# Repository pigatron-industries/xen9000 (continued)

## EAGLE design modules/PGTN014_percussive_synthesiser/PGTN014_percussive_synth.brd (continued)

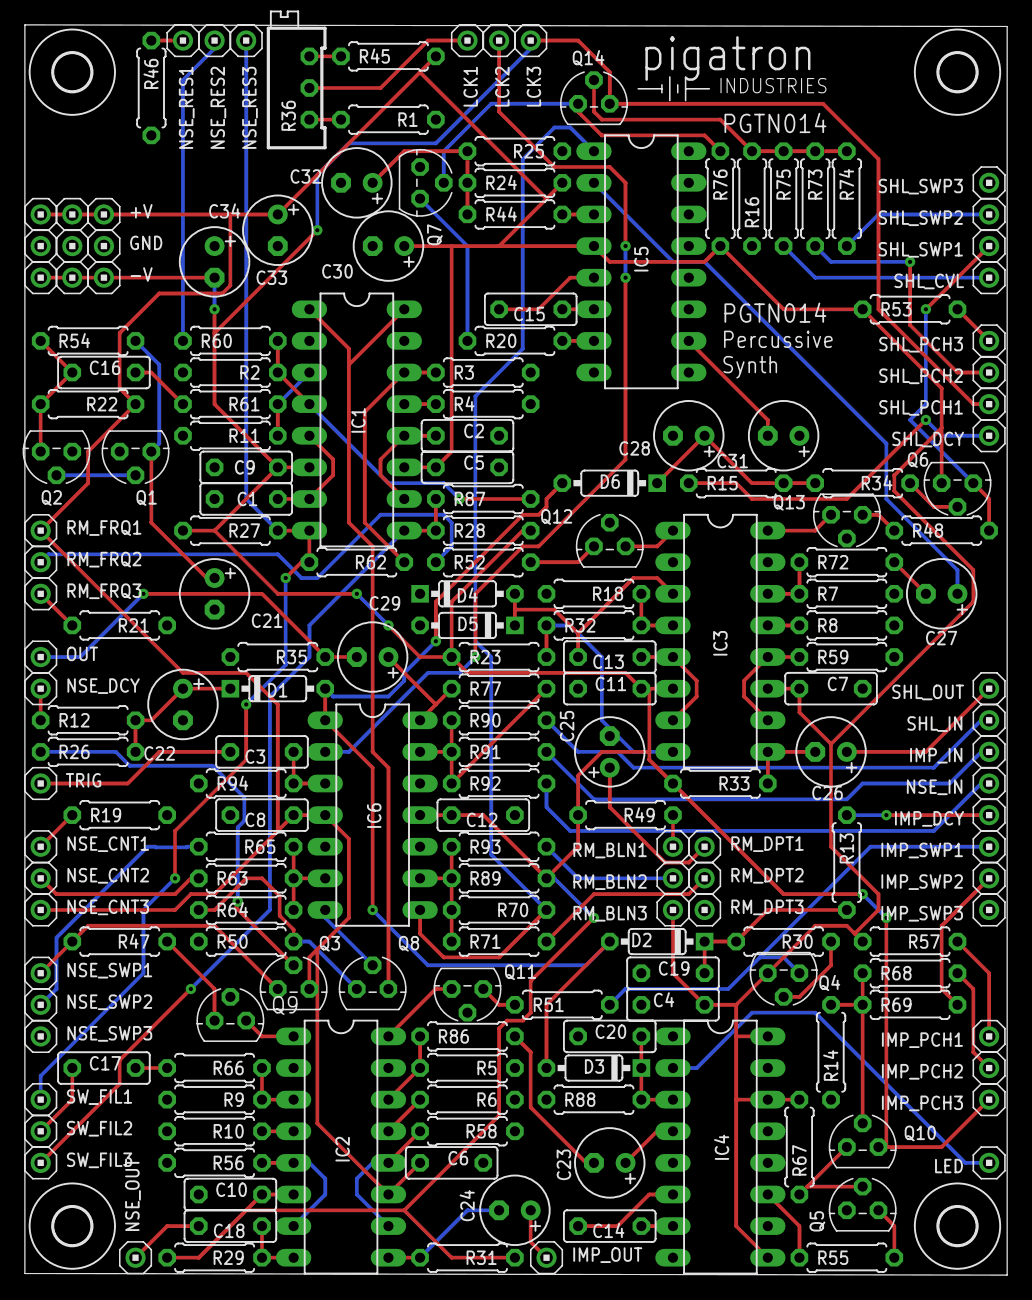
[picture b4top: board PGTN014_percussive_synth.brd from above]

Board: 2 copper layers, 78.9 x 100.4 mm, 201 parts (0 on the bottom side), 114 nets.

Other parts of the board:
U$1, U$2, U$3, U$4: STANDOFF/3.0
U$5: PIGATRON-LOGO

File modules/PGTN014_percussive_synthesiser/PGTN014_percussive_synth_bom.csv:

"Qty";"Value";"Device";"Package";"Parts";"Description";"SPICEPREFIX";
"1";"";"TRIMMER64X";"TRIMMER/64B";"R36";"Trimm resistor";"";
"1";"100R";"RESISTORRESISTOR/UPRIGHT/7.5";"RESISTOR/7.5";"R1";"RESISTOR, European symbol";"";
"18";"100k";"RESISTORRESISTOR/UPRIGHT/7.5";"RESISTOR/7.5";"R60, R61, R62, R63, R64, R65, R66, R67, R68, R69, R70, R71, R72, R73, R74, R75, R76, R77";"RESISTOR, European symbol";"";
"5";"100nF";"CAPACITORCERAMICDISC/5";"CERAMICDISC/5";"C16, C17, C18, C19, C20";"CAPACITOR, European symbol";"";
"10";"10k";"RESISTORRESISTOR/UPRIGHT/7.5";"RESISTOR/7.5";"R16, R26, R27, R28, R29, R30, R31, R32, R33, R34";"RESISTOR, European symbol";"";
"10";"10nF";"CAPACITORCERAMICDISC/5";"CERAMICDISC/5";"C4, C5, C6, C7, C8, C9, C10, C11, C12, C13";"CAPACITOR, European symbol";"";
"4";"10uF";"CAPACITOR/POLARIZEDE2.5-6";"E2,5-6";"C31, C32, C33, C34";"POLARIZED CAPACITOR, European symbol";"C";
"1";"12k";"RESISTORRESISTOR/UPRIGHT/7.5";"RESISTOR/7.5";"R44";"RESISTOR, European symbol";"";
"1";"180k";"RESISTORRESISTOR/UPRIGHT/7.5";"RESISTOR/7.5";"R86";"RESISTOR, European symbol";"";
"1";"1M";"RESISTORRESISTOR/UPRIGHT/7.5";"RESISTOR/7.5";"R94";"RESISTOR, European symbol";"";
"6";"1N4148";"1N4148DO35-7";"DO35-7";"D1, D2, D3, D4, D5, D6";"DIODE";"";
"4";"1k";"RESISTORRESISTOR/UPRIGHT/7.5";"RESISTOR/7.5";"R12, R13, R14, R15";"RESISTOR, European symbol";"";
"1";"1nF";"CAPACITORCERAMICDISC/5";"CERAMICDISC/5";"C3";"CAPACITOR, European symbol";"";
"2";"2.2k";"RESISTORRESISTOR/UPRIGHT/7.5";"RESISTOR/7.5";"R19, R20";"RESISTOR, European symbol";"";
"9";"2.2uF";"CAPACITOR/POLARIZEDE2.5-6";"E2,5-6";"C21, C22, C23, C24, C25, C26, C27, C28, C29";"POLARIZED CAPACITOR, European symbol";"C";
"6";"200k";"RESISTORRESISTOR/UPRIGHT/7.5";"RESISTOR/7.5";"R87, R88, R89, R90, R91, R92";"RESISTOR, European symbol";"";
"5";"20k";"RESISTORRESISTOR/UPRIGHT/7.5";"RESISTOR/7.5";"R35, R45, R46, R47, R48";"RESISTOR, European symbol";"";
"5";"220R";"RESISTORRESISTOR/UPRIGHT/7.5";"RESISTOR/7.5";"R2, R3, R4, R5, R6";"RESISTOR, European symbol";"";
"1";"22k";"RESISTORRESISTOR/UPRIGHT/7.5";"RESISTOR/7.5";"R49";"RESISTOR, European symbol";"";
"2";"22nF";"CAPACITORCERAMICDISC/5";"CERAMICDISC/5";"C14, C15";"CAPACITOR, European symbol";"";
"4";"27k";"RESISTORRESISTOR/UPRIGHT/7.5";"RESISTOR/7.5";"R50, R51, R52, R53";"RESISTOR, European symbol";"";
"8";"2N3904";"2N3904";"TO92";"Q1, Q2, Q3, Q4, Q5, Q6, Q7, Q9";"NPN Transistor";"";
"6";"2N3906";"2N3906";"TO92";"Q8, Q10, Q11, Q12, Q13, Q14";"PNP Transistor";"";
"1";"2k";"RESISTORRESISTOR/UPRIGHT/7.5";"RESISTOR/7.5";"R18";"RESISTOR, European symbol";"";
"1";"3.9k";"RESISTORRESISTOR/UPRIGHT/7.5";"RESISTOR/7.5";"R21";"RESISTOR, European symbol";"";
"1";"330k";"RESISTORRESISTOR/UPRIGHT/7.5";"RESISTOR/7.5";"R93";"RESISTOR, European symbol";"";
"2";"390R";"RESISTORRESISTOR/UPRIGHT/7.5";"RESISTOR/7.5";"R7, R8";"RESISTOR, European symbol";"";
"1";"4.7k";"RESISTORRESISTOR/UPRIGHT/7.5";"RESISTOR/7.5";"R22";"RESISTOR, European symbol";"";
"1";"4.7uF";"CAPACITOR/POLARIZEDE2.5-6";"E2,5-6";"C30";"POLARIZED CAPACITOR, European symbol";"C";
"1";"4046N";"4046N";"DIL16";"IC4";"Micropower PLL";"";
"2";"47k";"RESISTORRESISTOR/UPRIGHT/7.5";"RESISTOR/7.5";"R54, R55";"RESISTOR, European symbol";"";
"3";"5.1k";"RESISTORRESISTOR/UPRIGHT/7.5";"RESISTOR/7.5";"R23, R24, R25";"RESISTOR, European symbol";"";
"2";"560R";"RESISTORRESISTOR/UPRIGHT/7.5";"RESISTOR/7.5";"R9, R10";"RESISTOR, European symbol";"";
"4";"56k";"RESISTORRESISTOR/UPRIGHT/7.5";"RESISTOR/7.5";"R56, R57, R58, R59";"RESISTOR, European symbol";"";
"1";"820R";"RESISTORRESISTOR/UPRIGHT/7.5";"RESISTOR/7.5";"R11";"RESISTOR, European symbol";"";
"2";"820pF";"CAPACITORCERAMICDISC/5";"CERAMICDISC/5";"C1, C2";"CAPACITOR, European symbol";"";
"58";"HEADER/MALE/01";"HEADER/MALE/01";"HEADER/MALE/01";"+V, +V2, +V3, -V, -V2, -V3, GND, GND2, GND3, IMP_DCY, IMP_IN, IMP_OUT, IMP_PCH1, IMP_PCH2, IMP_PCH3, IMP_SWP1, IMP_SWP2, IMP_SWP3, LCK1, LCK2, LCK3, LED, NSE_CNT1, NSE_CNT2, NSE_CNT3, NSE_DCY, NSE_IN, NSE_OUT, NSE_RES1, NSE_RES2, NSE_RES3, NSE_SWP1, NSE_SWP2, NSE_SWP3, OUT, RM_BLN1, RM_BLN2, RM_BLN3, RM_DPT1, RM_DPT2, RM_DPT3, RM_FRQ1, RM_FRQ2, RM_FRQ3, SHL_CVL, SHL_DCY, SHL_IN, SHL_OUT, SHL_PCH1, SHL_PCH2, SHL_PCH3, SHL_SWP1, SHL_SWP2, SHL_SWP3, SW_FIL1, SW_FIL2, SW_FIL3, TRIG";"";"X";
"3";"LM13700N";"LM13700N";"DIL16";"IC1, IC2, IC3";"Dual OTA with buffers";"";
"1";"TL074P";"TL074P";"DIL14";"IC6";"OP AMP";"";
"1";"XR-2206";"DIL16";"DIL16";"IC5";"Dual In Line / Socket";"";

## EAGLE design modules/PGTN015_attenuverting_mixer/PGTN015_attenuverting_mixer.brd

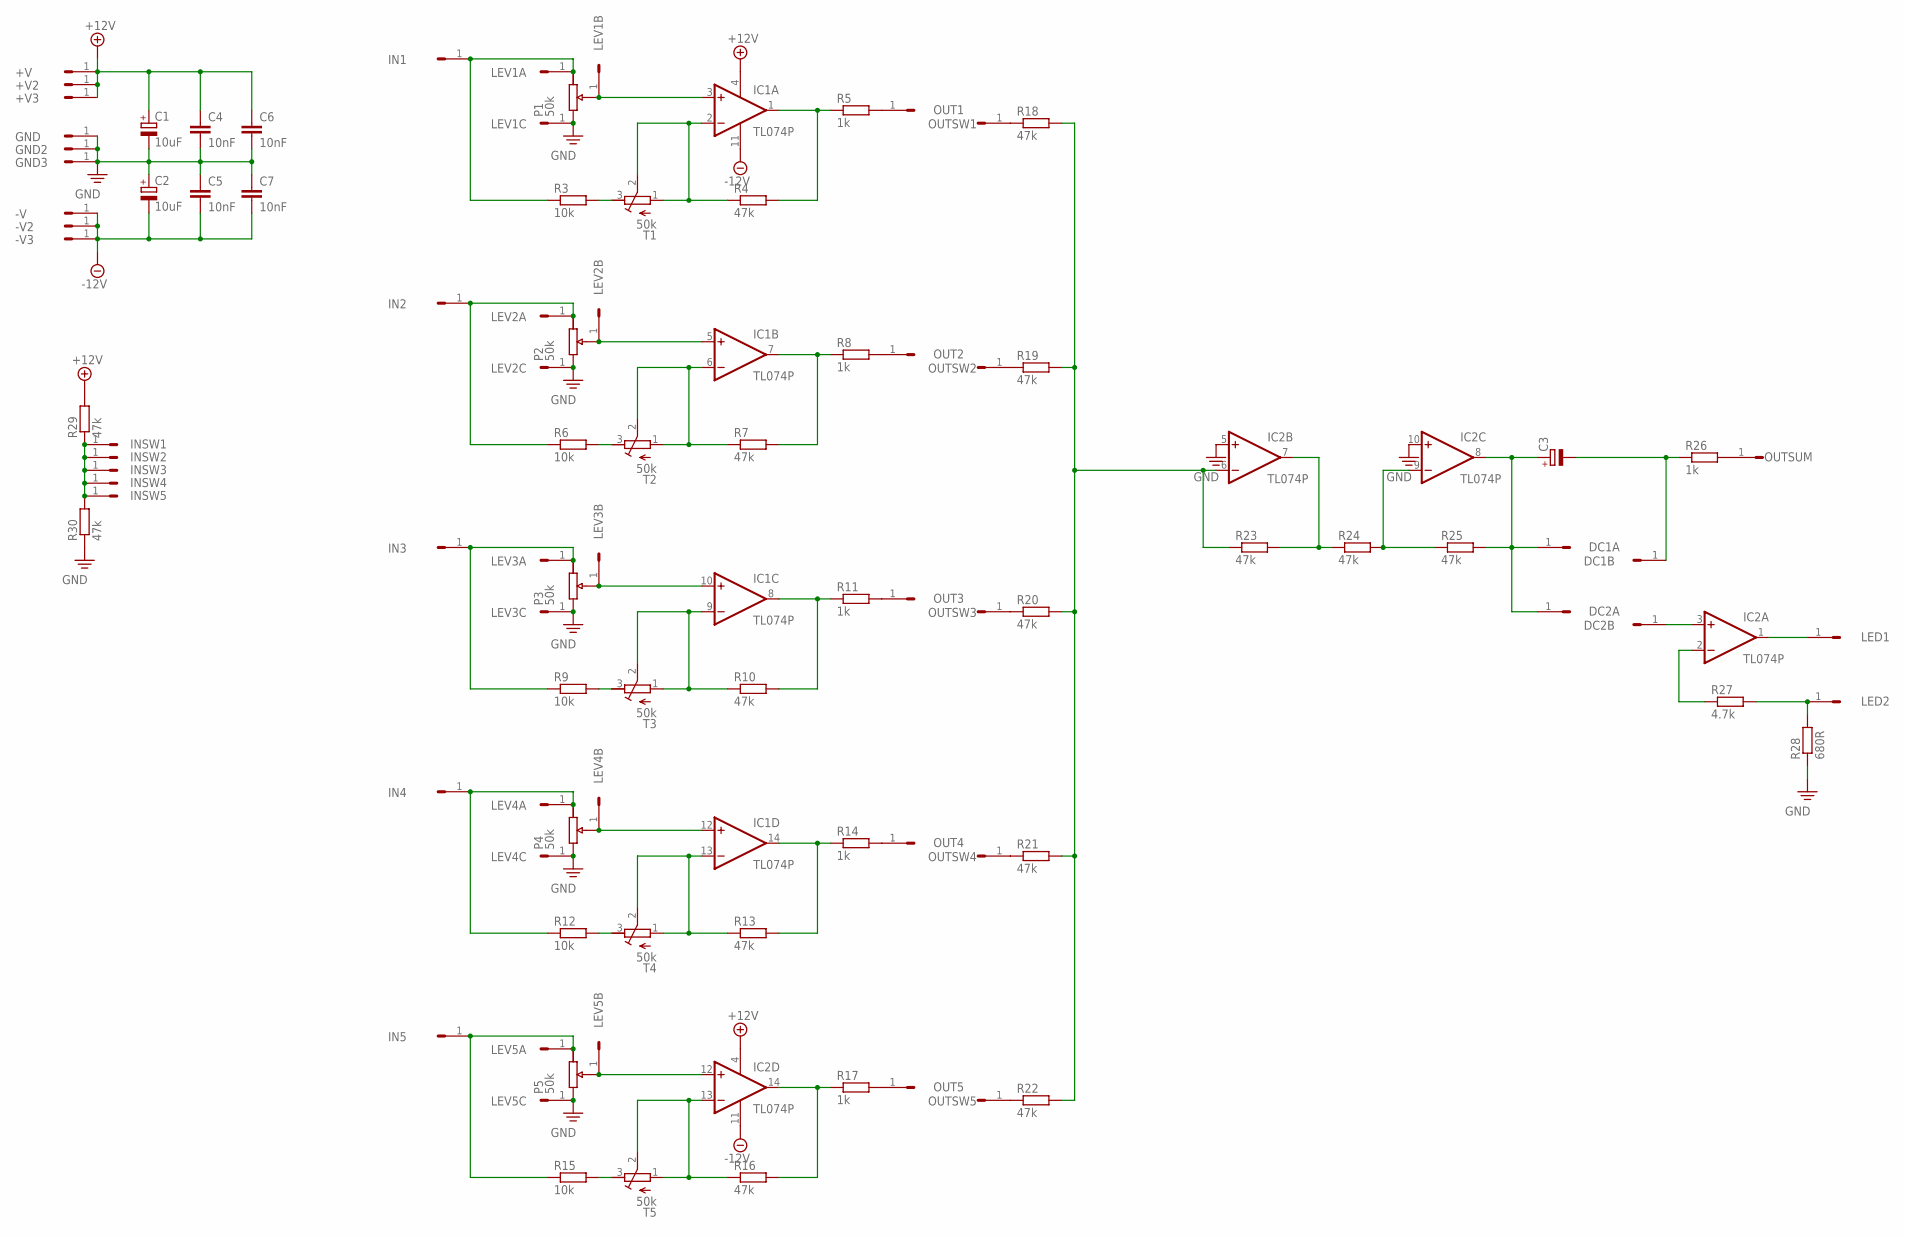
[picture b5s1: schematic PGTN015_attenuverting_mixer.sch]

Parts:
+V, +V2, +V3: HEADER/MALE/01
-V, -V2, -V3: HEADER/MALE/01
C1, C2: 10uF; E2,5-6
C3: CAPACITOR/POLARIZEDE2.5-6; E2,5-6
C4, C5, C6, C7: 10nF; CERAMICDISC/5
DC1A, DC1B, DC2A, DC2B: HEADER/MALE/01
GND, GND2, GND3: HEADER/MALE/01
IC1, IC2: TL074P; DIL14
IN1, IN2, IN3, IN4, IN5: HEADER/MALE/01
INSW1, INSW2, INSW3, INSW4, INSW5: HEADER/MALE/01
LED1, LED2: HEADER/MALE/01
LEV1A, LEV1B, LEV1C, LEV2A, LEV2B, LEV2C, LEV3A, LEV3B, LEV3C, LEV4A, LEV4B, LEV4C, LEV5A, LEV5B, LEV5C: HEADER/MALE/01
OUT1, OUT2, OUT3, OUT4, OUT5: HEADER/MALE/01
OUTSUM: HEADER/MALE/01
OUTSW1, OUTSW2, OUTSW3, OUTSW4, OUTSW5: HEADER/MALE/01
R3, R6, R9, R12, R15: 10k; RESISTOR/7.5
R4, R7, R10, R13, R16, R18, R19, R20, R21, R22, R23, R24, R25, R29, R30: 47k; RESISTOR/7.5
R5, R8, R11, R14, R17, R26: 1k; RESISTOR/7.5
R27: 4.7k; RESISTOR/7.5
R28: 680R; RESISTOR/7.5
T1, T2, T3, T4, T5: 50k; TRIMMER/64B

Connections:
+12V: +V.1, +V2.1, +V3.1, C1.+, C4.1, C6.1, IC1.4 (V+), IC2.4 (V+), R29.2
-12V: -V.1, -V2.1, -V3.1, C2.-, C5.2, C7.2, IC1.11 (V-), IC2.11 (V-)
GND: C1.-, C2.+, C4.2, C5.1, C6.2, C7.1, GND.1, GND2.1, GND3.1, IC2.5 (+IN), IC2.10 (+IN), LEV1C.1, LEV2C.1, LEV3C.1, LEV4C.1, LEV5C.1, R28.1, R30.1
unnamed: IC1.2 (-IN), R4.1, T1.1 (E), T1.2 (S)
unnamed: IC1.3 (+IN), LEV1B.1
unnamed: R3.2, T1.3 (A)
unnamed: IC1.1 (OUT), R4.2, R5.1
unnamed: IN1.1, LEV1A.1, R3.1
unnamed: OUT1.1, R5.2
unnamed: IC1.6 (-IN), R7.1, T2.1 (E), T2.2 (S)
unnamed: R6.2, T2.3 (A)
unnamed: IC1.7 (OUT), R7.2, R8.1
unnamed: IC1.5 (+IN), LEV2B.1
unnamed: IN2.1, LEV2A.1, R6.1
unnamed: OUT2.1, R8.2
unnamed: IC1.9 (-IN), R10.1, T3.1 (E), T3.2 (S)
unnamed: R9.2, T3.3 (A)
unnamed: IC1.8 (OUT), R10.2, R11.1
unnamed: IC1.10 (+IN), LEV3B.1
unnamed: IN3.1, LEV3A.1, R9.1
unnamed: OUT3.1, R11.2
unnamed: IC1.13 (-IN), R13.1, T4.1 (E), T4.2 (S)
unnamed: R12.2, T4.3 (A)
unnamed: IC1.14 (OUT), R13.2, R14.1
unnamed: IC1.12 (+IN), LEV4B.1
unnamed: IN4.1, LEV4A.1, R12.1
unnamed: OUT4.1, R14.2
unnamed: IC2.13 (-IN), R16.1, T5.1 (E), T5.2 (S)
unnamed: R15.2, T5.3 (A)
unnamed: IC2.14 (OUT), R16.2, R17.1
unnamed: IC2.12 (+IN), LEV5B.1
unnamed: IN5.1, LEV5A.1, R15.1
unnamed: OUT5.1, R17.2
unnamed: OUTSW1.1, R18.1
unnamed: OUTSW2.1, R19.1
unnamed: OUTSW3.1, R20.1
unnamed: OUTSW4.1, R21.1
unnamed: OUTSW5.1, R22.1
unnamed: C3.-, DC1B.1, R26.1
unnamed: IC2.7 (OUT), R23.2, R24.1
unnamed: IC2.6 (-IN), R18.2, R19.2, R20.2, R21.2, R22.2, R23.1
unnamed: IC2.9 (-IN), R24.2, R25.1
unnamed: C3.+, DC1A.1, DC2A.1, IC2.8 (OUT), R25.2
unnamed: OUTSUM.1, R26.2
unnamed: DC2B.1, IC2.3 (+IN)
unnamed: IC2.2 (-IN), R27.1
unnamed: LED2.1, R27.2, R28.2
unnamed: IC2.1 (OUT), LED1.1
unnamed: INSW1.1, INSW2.1, INSW3.1, INSW4.1, INSW5.1, R29.1, R30.2

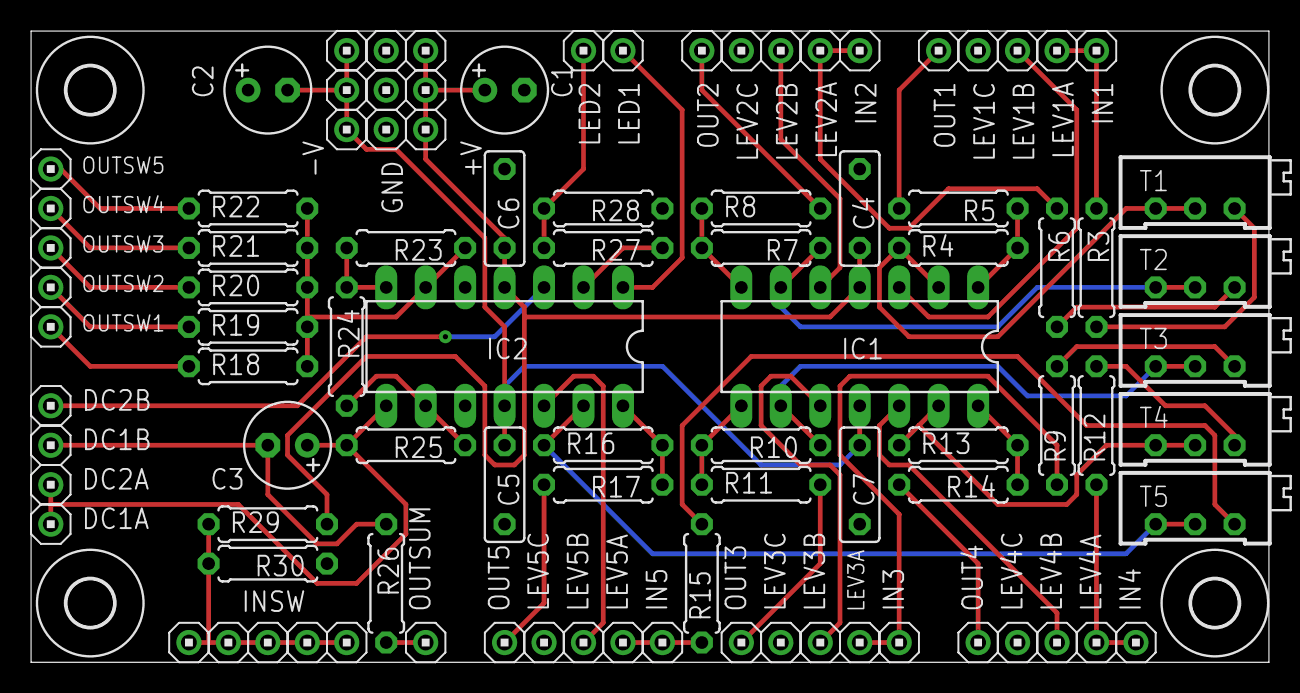
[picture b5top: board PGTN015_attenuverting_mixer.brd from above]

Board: 2 copper layers, 79.7 x 40.6 mm, 98 parts (1 on the bottom side), 49 nets.

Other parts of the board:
U$1, U$2, U$3, U$4: STANDOFF/3.0
U$5: PIGATRON-LOGO

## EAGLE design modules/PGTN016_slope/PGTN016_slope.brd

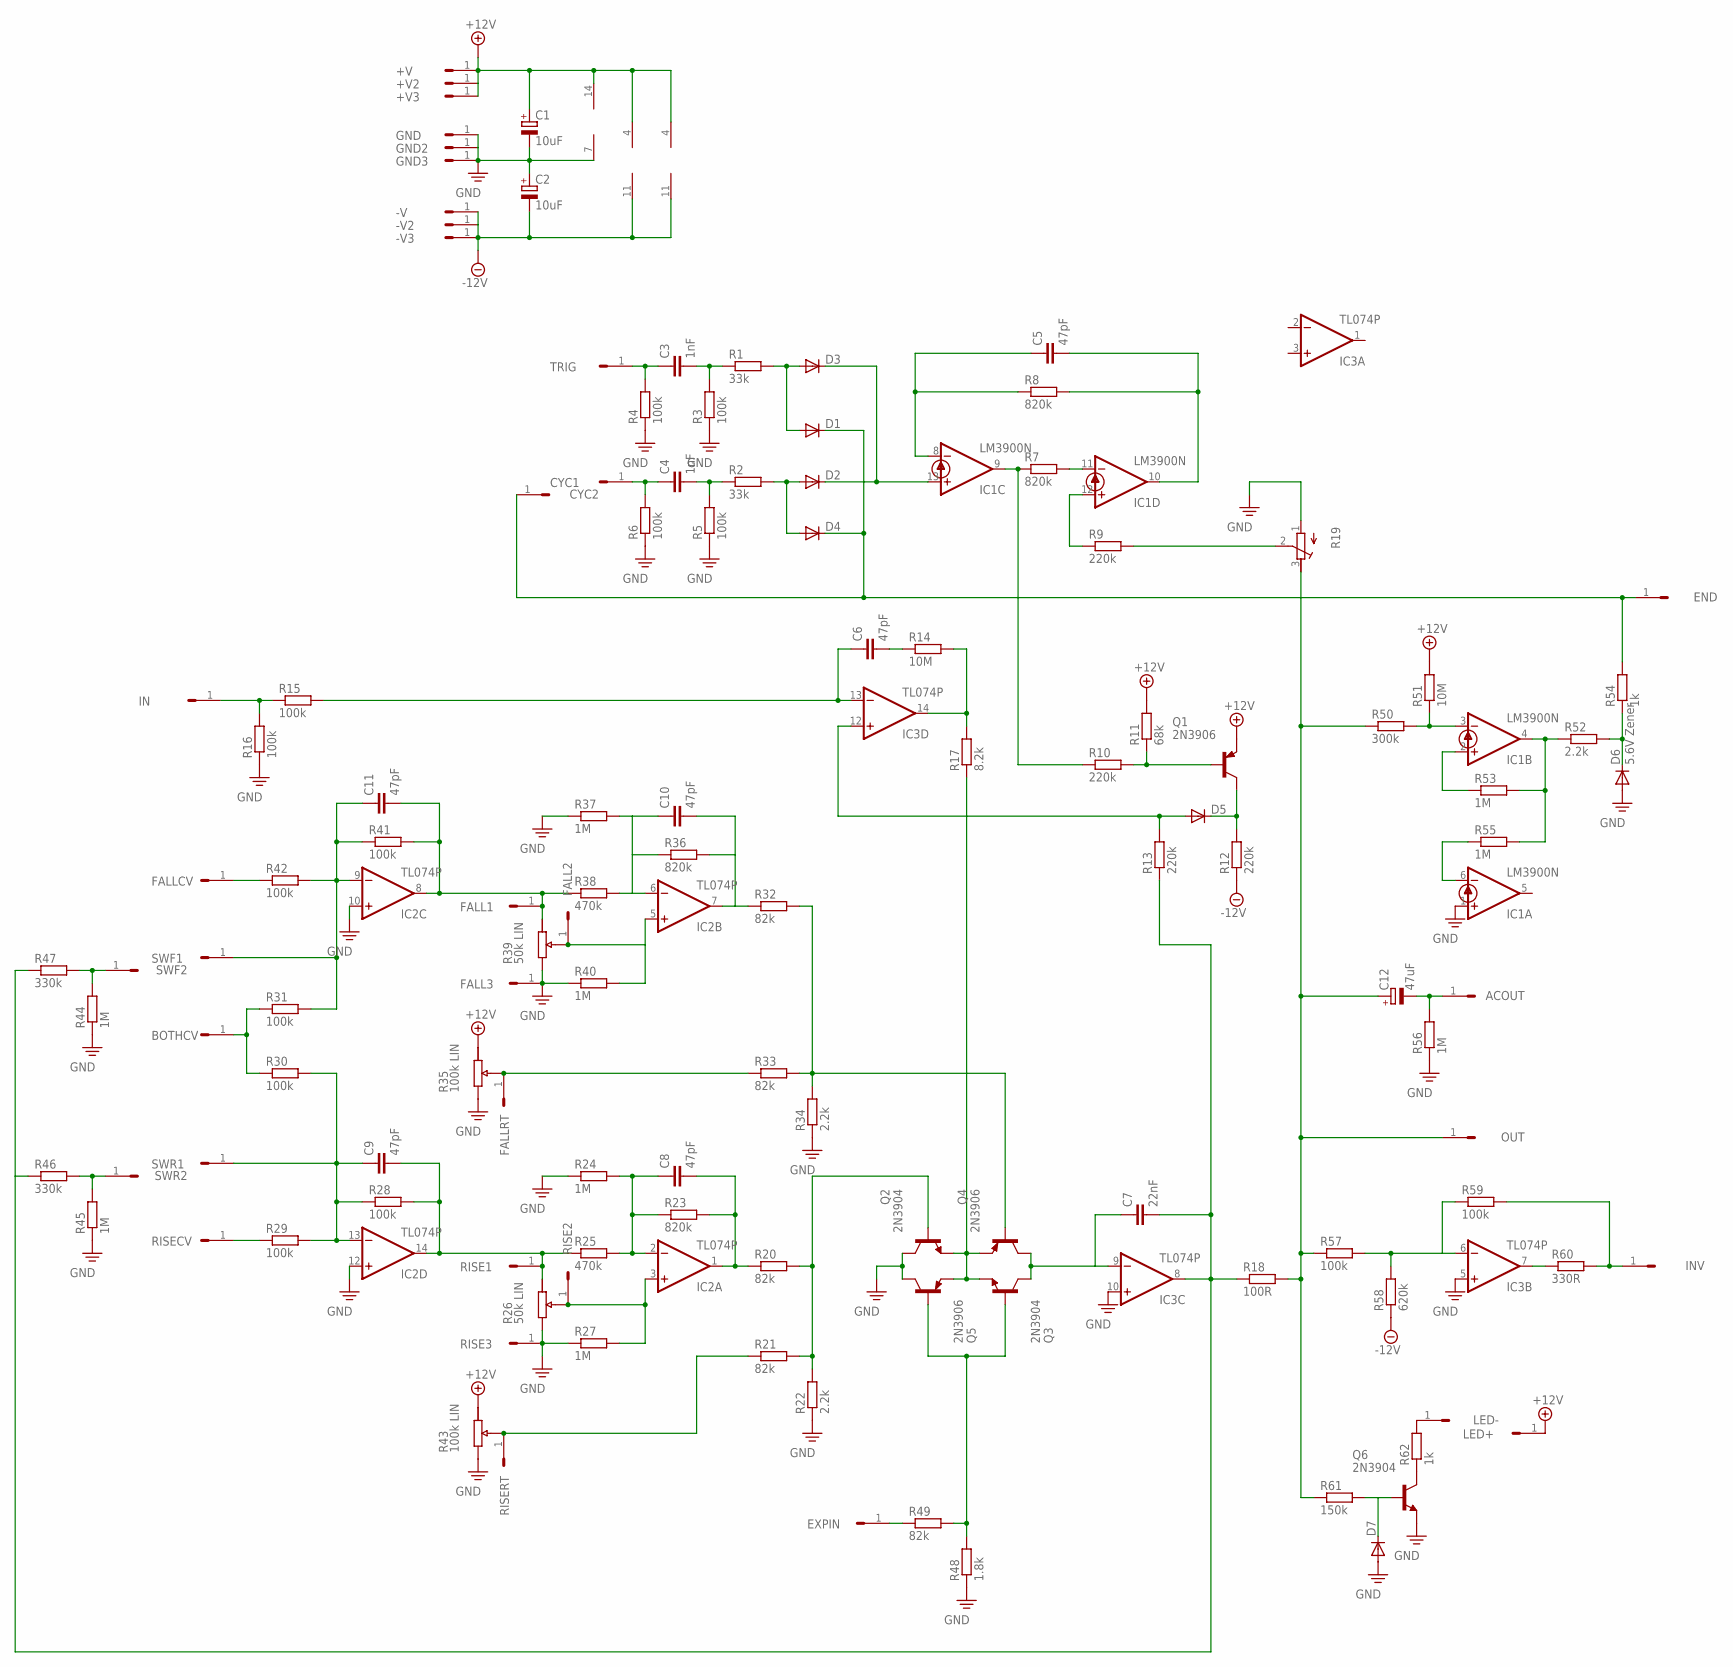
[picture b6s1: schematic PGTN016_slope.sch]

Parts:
+V, +V2, +V3: HEADER/MALE/01
-V, -V2, -V3: HEADER/MALE/01
ACOUT: HEADER/MALE/01
BOTHCV: HEADER/MALE/01
C1, C2: 10uF; E2,5-6
C3, C4: 1nF; CERAMICDISC/5
C5, C6, C8, C9, C10, C11: 47pF; CERAMICDISC/5
C7: 22nF; CERAMICDISC/5
C12: 47uF; E2,5-6
CYC1, CYC2: HEADER/MALE/01
D1, D2, D3, D4, D5, D7: 1N4148DO35-7; DO35-7
D6: 5.6V Zener; DO35-7
END: HEADER/MALE/01
EXPIN: HEADER/MALE/01
FALL1, FALL2, FALL3: HEADER/MALE/01
FALLCV: HEADER/MALE/01
FALLRT: HEADER/MALE/01
GND, GND2, GND3: HEADER/MALE/01
IC1: LM3900N; DIL14
IC2, IC3: TL074P; DIL14
IN: HEADER/MALE/01
INV: HEADER/MALE/01
LED+: HEADER/MALE/01
LED-: HEADER/MALE/01
OUT: HEADER/MALE/01
Q1, Q4, Q5: 2N3906; TO92
Q2, Q3, Q6: 2N3904; TO92
R1, R2: 33k; RESISTOR/7.5
R3, R4, R5, R6, R15, R16, R28, R29, R30, R31, R41, R42, R57, R59: 100k; RESISTOR/7.5
R7, R8, R23, R36: 820k; RESISTOR/7.5
R9, R10, R12, R13: 220k; RESISTOR/7.5
R11: 68k; RESISTOR/7.5
R14, R51: 10M; RESISTOR/7.5
R17: 8.2k; RESISTOR/7.5
R18: 100R; RESISTOR/7.5
R19: TRIMMER64X; TRIMMER/64B
R20, R21, R32, R33, R49: 82k; RESISTOR/7.5
R22, R34, R52: 2.2k; RESISTOR/7.5
R24, R27, R37, R40, R44, R45, R53, R55, R56: 1M; RESISTOR/7.5
R25, R38: 470k; RESISTOR/7.5
R46, R47: 330k; RESISTOR/7.5
R48: 1.8k; RESISTOR/7.5
R50: 300k; RESISTOR/7.5
R54, R62: 1k; RESISTOR/7.5
R58: 620k; RESISTOR/7.5
R60: 330R; RESISTOR/7.5
R61: 150k; RESISTOR/7.5
RISE1, RISE2, RISE3: HEADER/MALE/01
RISECV: HEADER/MALE/01
RISERT: HEADER/MALE/01
SWF1, SWF2: HEADER/MALE/01
SWR1, SWR2: HEADER/MALE/01
TRIG: HEADER/MALE/01

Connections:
+12V: +V.1, +V2.1, +V3.1, C1.+, IC1.14 (V+), IC2.4 (V+), IC3.4 (V+), LED+.1, Q1.3 (E), R11.2, R51.2
-12V: -V.1, -V2.1, -V3.1, C2.-, IC2.11 (V-), IC3.11 (V-), R12.1, R58.1
GND: C1.-, C2.+, D6.A, D7.A, FALL3.1, GND.1, GND2.1, GND3.1, IC1.1 (+IN), IC1.7 (GND), IC2.10 (+IN), IC2.12 (+IN), IC3.5 (+IN), IC3.10 (+IN), Q2.1 (C), Q5.1 (C), Q6.3 (E), R3.1, R4.1, R5.1, R6.1, R16.1, R19.1 (E), R22.1, R24.1, R27.1, R34.1, R37.1, R40.1, R44.1, R45.1, R48.1, R56.1, RISE3.1
unnamed: C4.2, R2.1, R5.2
unnamed: C4.1, CYC1.1, R6.2
unnamed: D2.C, D3.C, IC1.13 (+IN)
unnamed: Q1.2 (B), R10.2, R11.1
unnamed: CYC2.1, D1.C, D4.C, END.1, R54.2
unnamed: D2.A, D4.A, R2.2
unnamed: D1.A, D3.A, R1.2
unnamed: C3.2, R1.1, R3.2
unnamed: C3.1, R4.2, TRIG.1
unnamed: IC1.9 (OUT), R7.1, R10.1
unnamed: IC1.11 (-IN), R7.2
unnamed: C5.2, IC1.10 (OUT), R8.2
unnamed: C5.1, IC1.8 (-IN), R8.1
unnamed: IC1.12 (+IN), R9.1
unnamed: D5.C, Q1.1 (C), R12.2
unnamed: D5.A, IC3.12 (+IN), R13.2
unnamed: Q2.3 (E), Q3.3 (E), Q4.3 (E), Q5.3 (E), R17.1
unnamed: IC3.14 (OUT), R14.2, R17.2
unnamed: C6.2, R14.1
unnamed: C6.1, IC3.13 (-IN), R15.2
unnamed: IN.1, R15.1, R16.2
unnamed: EXPIN.1, R49.1
unnamed: C7.1, IC3.9 (-IN), Q3.1 (C), Q4.1 (C)
unnamed: C12.+, OUT.1, R18.2, R19.3 (A), R50.1, R57.1, R61.1
unnamed: Q3.2 (B), Q5.2 (B), R48.2, R49.2
unnamed: R9.2, R19.2 (S)
unnamed: IC2.3 (+IN), R27.2, RISE2.1
unnamed: Q2.2 (B), R20.2, R21.2, R22.2
unnamed: C8.2, IC2.1 (OUT), R20.1, R23.2
unnamed: C8.1, IC2.2 (-IN), R23.1, R24.2, R25.2
unnamed: BOTHCV.1, R30.1, R31.1
unnamed: C10.2, IC2.7 (OUT), R32.1, R36.2
unnamed: Q4.2 (B), R32.2, R33.2, R34.2
unnamed: C9.2, IC2.14 (OUT), R25.1, R28.2, RISE1.1
unnamed: C9.1, IC2.13 (-IN), R28.1, R29.2, R30.2, SWR1.1
unnamed: R29.1, RISECV.1
unnamed: C10.1, IC2.6 (-IN), R36.1, R37.2, R38.2
unnamed: FALLRT.1, R33.1
unnamed: FALL2.1, IC2.5 (+IN), R40.2
unnamed: C11.1, IC2.9 (-IN), R31.2, R41.1, R42.2, SWF1.1
unnamed: R21.1, RISERT.1
unnamed: C11.2, FALL1.1, IC2.8 (OUT), R38.1, R41.2
unnamed: FALLCV.1, R42.1
unnamed: R45.2, R46.2, SWR2.1
unnamed: R44.2, R47.2, SWF2.1
unnamed: C7.2, IC3.8 (OUT), R13.1, R18.1, R46.1, R47.1
unnamed: IC1.3 (-IN), R50.2, R51.1
unnamed: IC1.4 (OUT), R52.1, R53.2, R55.2
unnamed: IC1.6 (-IN), R55.1
unnamed: IC1.2 (+IN), R53.1
unnamed: D6.C, R52.2, R54.1
unnamed: ACOUT.1, C12.-, R56.2
unnamed: IC3.6 (-IN), R57.2, R58.2, R59.1
unnamed: IC3.7 (OUT), R60.1
unnamed: INV.1, R59.2, R60.2
unnamed: D7.C, Q6.2 (B), R61.2
unnamed: Q6.1 (C), R62.1
unnamed: LED-.1, R62.2

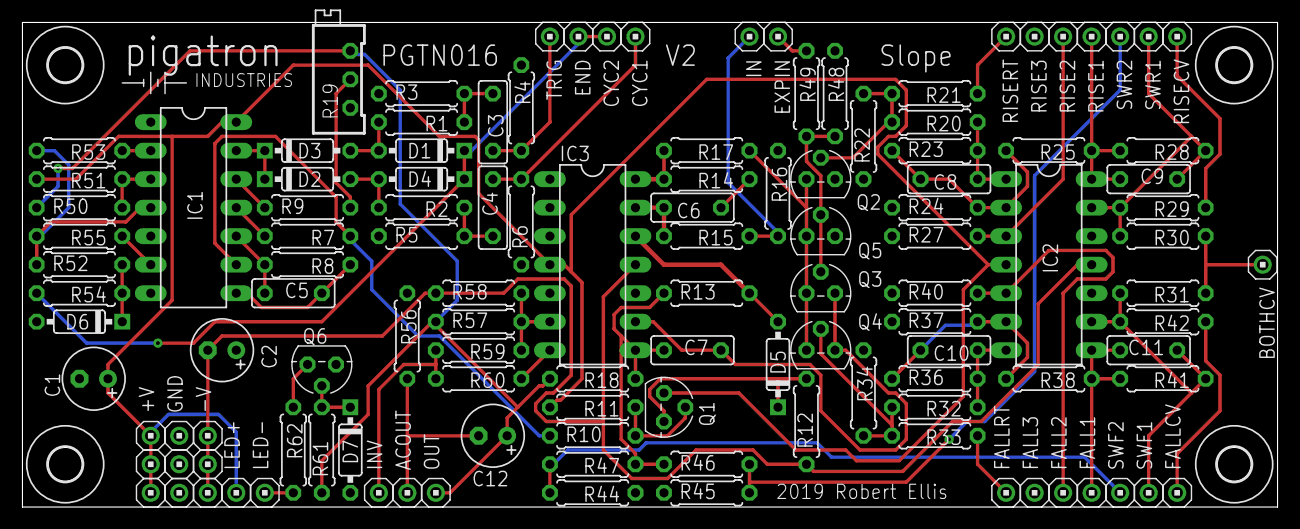
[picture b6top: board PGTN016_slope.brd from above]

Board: 2 copper layers, 111.8 x 43.2 mm, 126 parts (0 on the bottom side), 61 nets.

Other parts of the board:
U$1, U$2, U$3, U$4: STANDOFF/3.0
U$5: PIGATRON-LOGO

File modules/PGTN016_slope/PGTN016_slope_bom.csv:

"Qty";"Value";"Device";"Package";"Parts";"Description";"SPICEPREFIX";
"6";"";"1N4148DO35-7";"DO35-7";"D1, D2, D3, D4, D5, D7";"DIODE";"";
"1";"";"CAPACITOR/POLARIZEDE2.5-6";"E2,5-6";"C12";"POLARIZED CAPACITOR, European symbol";"";
"1";"";"TRIMMER64X";"TRIMMER/64B";"R19";"Trimm resistor";"";
"1";"1.8k";"RESISTORRESISTOR/UPRIGHT/7.5";"RESISTOR/7.5";"R48";"RESISTOR, European symbol";"";
"1";"100R";"RESISTORRESISTOR/UPRIGHT/7.5";"RESISTOR/7.5";"R18";"RESISTOR, European symbol";"";
"14";"100k";"RESISTORRESISTOR/UPRIGHT/7.5";"RESISTOR/7.5";"R3, R4, R5, R6, R15, R16, R28, R29, R30, R31, R41, R42, R57, R59";"RESISTOR, European symbol";"";
"2";"10M";"RESISTORRESISTOR/UPRIGHT/7.5";"RESISTOR/7.5";"R14, R51";"RESISTOR, European symbol";"";
"2";"10uF";"CAPACITOR/POLARIZEDE2.5-6";"E2,5-6";"C1, C2";"POLARIZED CAPACITOR, European symbol";"C";
"1";"150k";"RESISTORRESISTOR/UPRIGHT/7.5";"RESISTOR/7.5";"R61";"RESISTOR, European symbol";"";
"9";"1M";"RESISTORRESISTOR/UPRIGHT/7.5";"RESISTOR/7.5";"R24, R27, R37, R40, R44, R45, R53, R55, R56";"RESISTOR, European symbol";"";
"2";"1k";"RESISTORRESISTOR/UPRIGHT/7.5";"RESISTOR/7.5";"R54, R62";"RESISTOR, European symbol";"";
"2";"1nF";"CAPACITORCERAMICDISC/5";"CERAMICDISC/5";"C3, C4";"CAPACITOR, European symbol";"";
"3";"2.2k";"RESISTORRESISTOR/UPRIGHT/7.5";"RESISTOR/7.5";"R22, R34, R52";"RESISTOR, European symbol";"";
"4";"220k";"RESISTORRESISTOR/UPRIGHT/7.5";"RESISTOR/7.5";"R9, R10, R12, R13";"RESISTOR, European symbol";"";
"1";"22nF";"CAPACITORCERAMICDISC/5";"CERAMICDISC/5";"C7";"CAPACITOR, European symbol";"";
"3";"2N3904";"2N3904";"TO92";"Q2, Q3, Q6";"NPN Transistor";"";
"3";"2N3906";"2N3906";"TO92";"Q1, Q4, Q5";"PNP Transistor";"";
"1";"300k";"RESISTORRESISTOR/UPRIGHT/7.5";"RESISTOR/7.5";"R50";"RESISTOR, European symbol";"";
"1";"330R";"RESISTORRESISTOR/UPRIGHT/7.5";"RESISTOR/7.5";"R60";"RESISTOR, European symbol";"";
"2";"330k";"RESISTORRESISTOR/UPRIGHT/7.5";"RESISTOR/7.5";"R46, R47";"RESISTOR, European symbol";"";
"2";"33k";"RESISTORRESISTOR/UPRIGHT/7.5";"RESISTOR/7.5";"R1, R2";"RESISTOR, European symbol";"";
"2";"470k";"RESISTORRESISTOR/UPRIGHT/7.5";"RESISTOR/7.5";"R25, R38";"RESISTOR, European symbol";"";
"6";"47pF";"CAPACITORCERAMICDISC/5";"CERAMICDISC/5";"C5, C6, C8, C9, C10, C11";"CAPACITOR, European symbol";"";
"1";"5.6V Zener";"1N4148DO35-7";"DO35-7";"D6";"DIODE";"";
"1";"620k";"RESISTORRESISTOR/UPRIGHT/7.5";"RESISTOR/7.5";"R58";"RESISTOR, European symbol";"";
"1";"68k";"RESISTORRESISTOR/UPRIGHT/7.5";"RESISTOR/7.5";"R11";"RESISTOR, European symbol";"";
"1";"8.2k";"RESISTORRESISTOR/UPRIGHT/7.5";"RESISTOR/7.5";"R17";"RESISTOR, European symbol";"";
"4";"820k";"RESISTORRESISTOR/UPRIGHT/7.5";"RESISTOR/7.5";"R7, R8, R23, R36";"RESISTOR, European symbol";"";
"5";"82k";"RESISTORRESISTOR/UPRIGHT/7.5";"RESISTOR/7.5";"R20, R21, R32, R33, R49";"RESISTOR, European symbol";"";
"35";"HEADER/MALE/01";"HEADER/MALE/01";"HEADER/MALE/01";"+V, +V2, +V3, -V, -V2, -V3, ACOUT, BOTHCV, CYC1, CYC2, END, EXPIN, FALL1, FALL2, FALL3, FALLCV, FALLRT, GND, GND2, GND3, IN, INV, LED+, LED-, OUT, RISE1, RISE2, RISE3, RISECV, RISERT, SWF1, SWF2, SWR1, SWR2, TRIG";"";"X";
"1";"LM3900N";"LM3900N";"DIL14";"IC1";"OP AMP";"";
"2";"TL074P";"TL074P";"DIL14";"IC2, IC3";"OP AMP";"";

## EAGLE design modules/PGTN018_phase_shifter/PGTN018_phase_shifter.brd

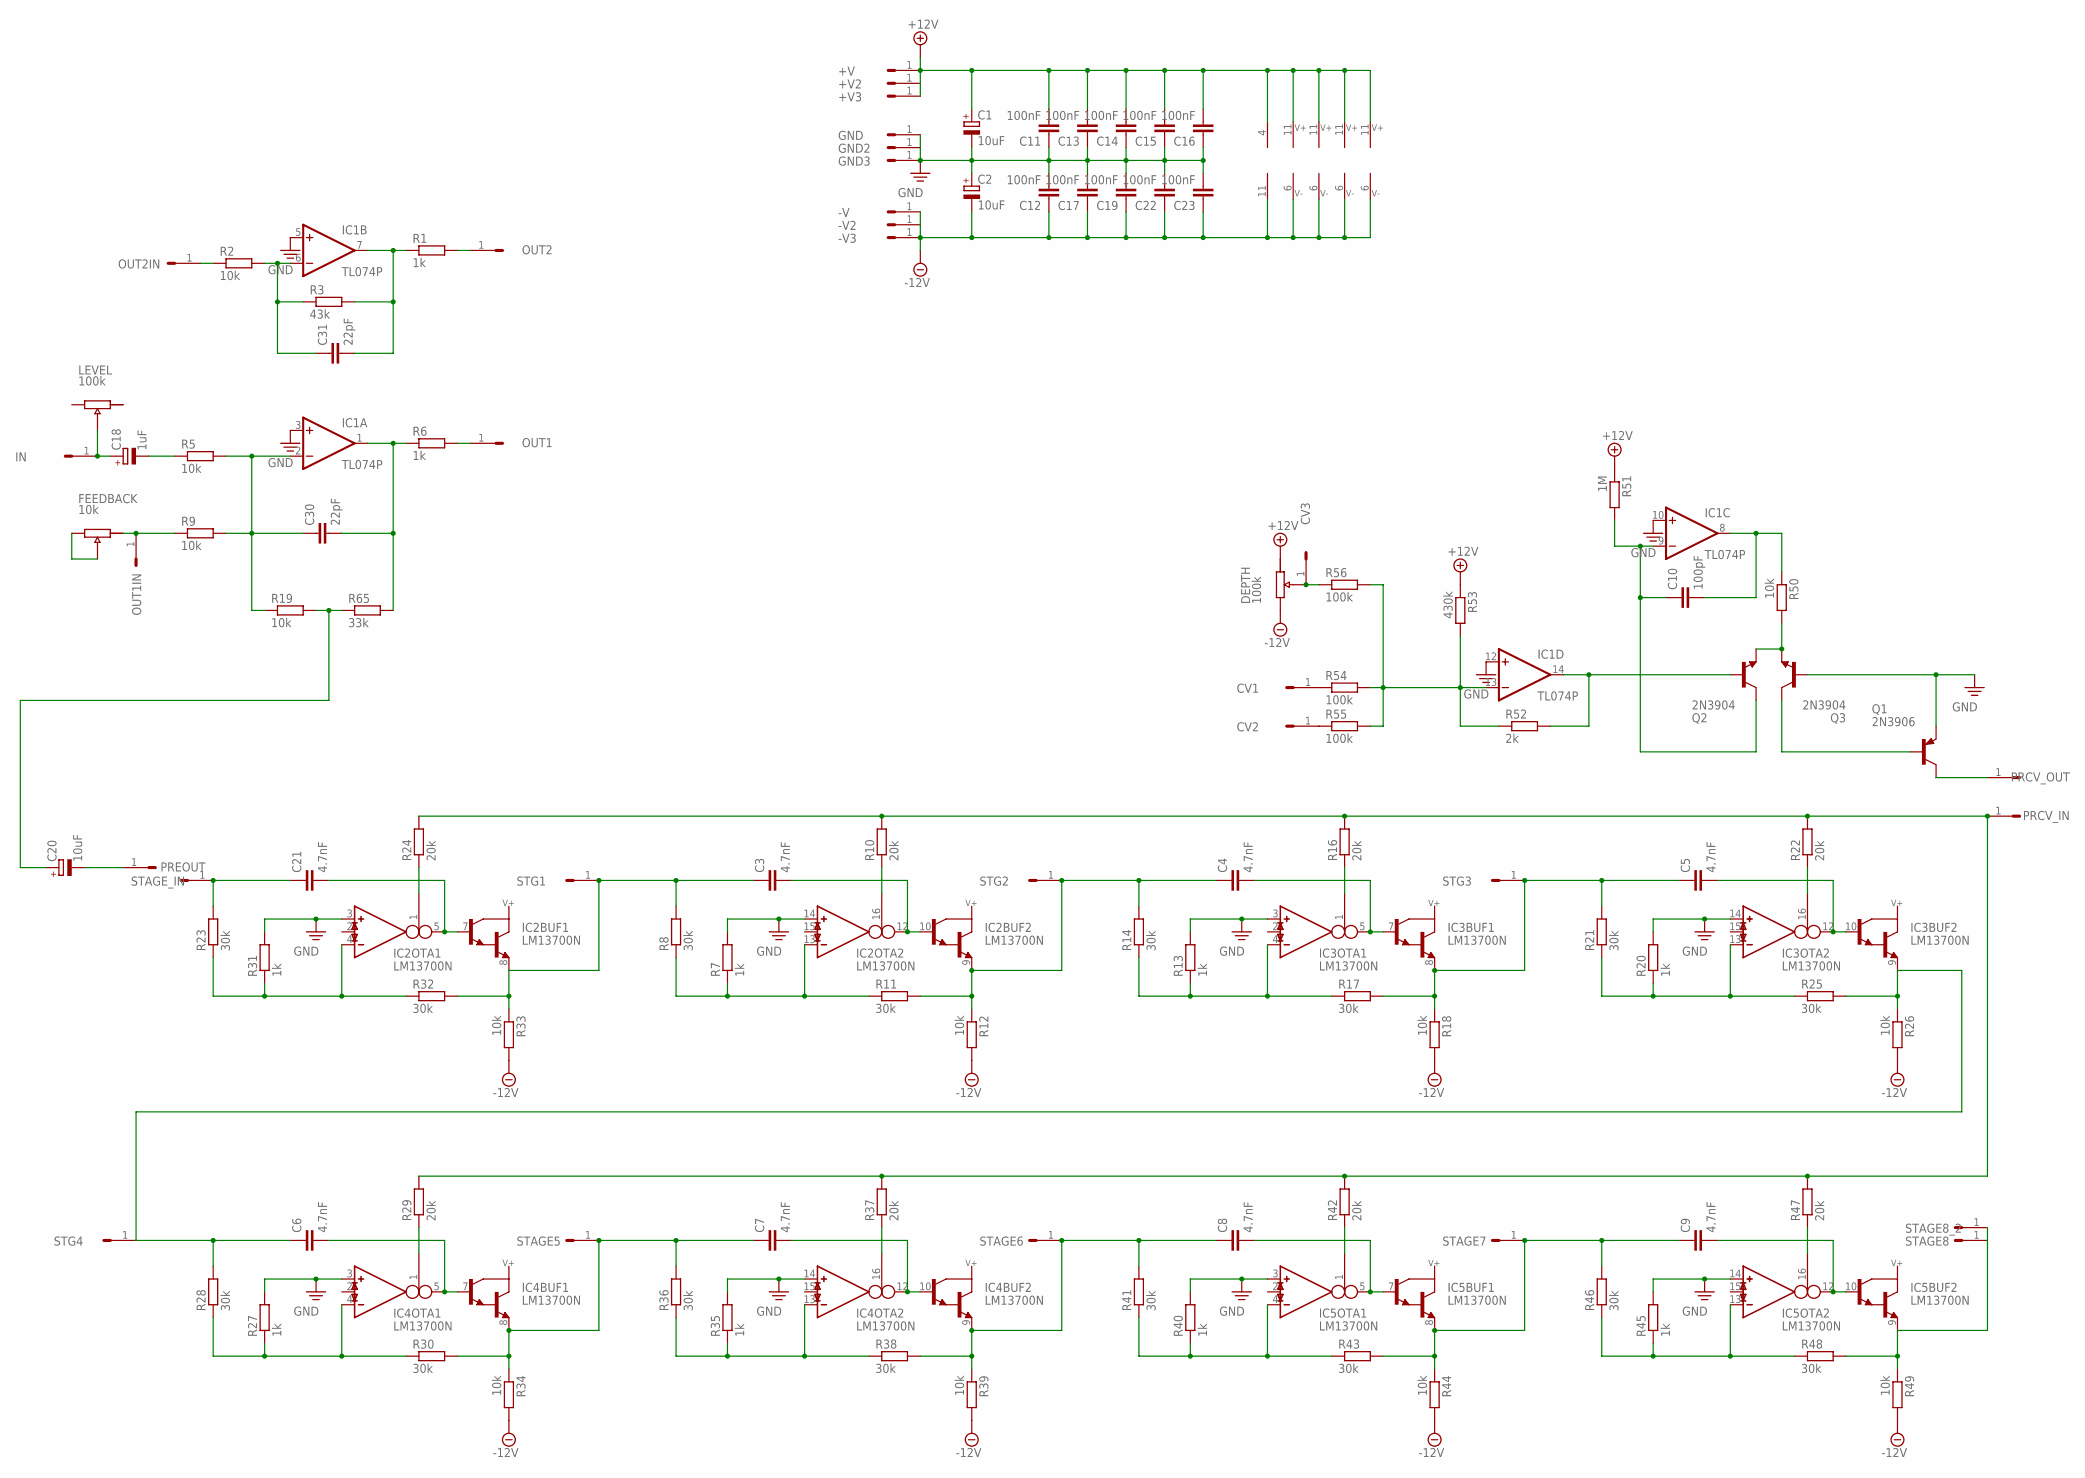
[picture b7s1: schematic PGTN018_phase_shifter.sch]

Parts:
+V, +V2, +V3: HEADER/MALE/01
-V, -V2, -V3: HEADER/MALE/01
C1, C2, C20: 10uF; E2,5-6
C3, C4, C5, C6, C7, C8, C9, C21: 4.7nF; CERAMICDISC/5
C10: 100pF; CERAMICDISC/5
C11, C12, C13, C14, C15, C16, C17, C19, C22, C23: 100nF; CERAMICDISC/5
C18: 1uF; E2,5-6
C30, C31: 22pF; CERAMICDISC/5
CV1, CV2, CV3: HEADER/MALE/01
GND, GND2, GND3: HEADER/MALE/01
IC1: TL074P; DIL14
IC2, IC3, IC4, IC5: LM13700N; DIL16
IN: HEADER/MALE/01
OUT1, OUT1IN, OUT2, OUT2IN: HEADER/MALE/01
PRCV_IN: HEADER/MALE/01
PRCV_OUT: HEADER/MALE/01
PREOUT: HEADER/MALE/01
Q1: 2N3906; TO92
Q2, Q3: 2N3904; TO92
R1, R6, R7, R13, R20, R27, R31, R35, R40, R45: 1k; RESISTOR/7.5
R2, R5, R9, R12, R18, R19, R26, R33, R34, R39, R44, R49, R50: 10k; RESISTOR/7.5
R3: 43k; RESISTOR/7.5
R8, R11, R14, R17, R21, R23, R25, R28, R30, R32, R36, R38, R41, R43, R46, R48: 30k; RESISTOR/7.5
R10, R16, R22, R24, R29, R37, R42, R47: 20k; RESISTOR/7.5
R51: 1M; RESISTOR/7.5
R52: 2k; RESISTOR/7.5
R53: 430k; RESISTOR/7.5
R54, R55, R56: 100k; RESISTOR/7.5
R65: 33k; RESISTOR/7.5
STAGE5, STAGE6, STAGE7, STAGE8, STAGE8_2: HEADER/MALE/01
STAGE_IN: HEADER/MALE/01
STG1, STG2, STG3, STG4: HEADER/MALE/01

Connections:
+12V: R51.1, R53.1
-12V: R12.2, R18.2, R26.2, R33.2, R34.2, R39.2, R44.2, R49.2
GND: C1.-, C2.+, C11.1, C12.2, C13.1, C14.1, C15.1, C16.1, C17.2, C19.2, C22.2, C23.2, GND.1, GND2.1, GND3.1
unnamed: OUT2.1, R1.2
unnamed: C30.1, IC1.2 (-IN), R5.2, R9.2, R19.1
unnamed: C31.2, IC1.7 (OUT), R1.1, R3.2
unnamed: C31.1, IC1.6 (-IN), R2.2, R3.1
unnamed: C30.2, IC1.1 (OUT), R6.1, R65.2
unnamed: C18.+, IN.1
unnamed: C18.-, R5.1
unnamed: OUT1.1, R6.2
unnamed: OUT2IN.1, R2.1
unnamed: OUT1IN.1, R9.1
unnamed: C20.+, R19.2, R65.1
unnamed: C20.-, PREOUT.1
unnamed: C21.1, R23.2, STAGE_IN.1
unnamed: IC2.4 (IN_N), R23.1, R31.1, R32.1
unnamed: C3.1, IC2.8 (E), R8.2, R32.2, R33.1, STG1.1
unnamed: IC2.1 (I_BIAS), R24.1
unnamed: C21.2, IC2.5 (OUT), IC2.7 (B)
unnamed: IC2.13 (IN_N), R7.1, R8.1, R11.1
unnamed: IC3.4 (IN_N), R13.1, R14.1, R17.1
unnamed: IC2.16 (I_BIAS), R10.1
unnamed: C3.2, IC2.10 (B), IC2.12 (OUT)
unnamed: C4.1, IC2.9 (E), R11.2, R12.1, R14.2, STG2.1
unnamed: C6.1, IC3.9 (E), R25.2, R26.1, R28.2, STG4.1
unnamed: IC3.1 (I_BIAS), R16.1
unnamed: C4.2, IC3.5 (OUT), IC3.7 (B)
unnamed: C5.1, IC3.8 (E), R17.2, R18.1, R21.2, STG3.1
unnamed: IC3.13 (IN_N), R20.1, R21.1, R25.1
unnamed: IC3.16 (I_BIAS), R22.1
unnamed: C5.2, IC3.10 (B), IC3.12 (OUT)
unnamed: PRCV_IN.1, R10.2, R16.2, R22.2, R24.2, R29.2, R37.2, R42.2, R47.2
unnamed: IC4.4 (IN_N), R27.1, R28.1, R30.1
unnamed: IC4.1 (I_BIAS), R29.1
unnamed: C6.2, IC4.5 (OUT), IC4.7 (B)
unnamed: C7.1, IC4.8 (E), R30.2, R34.1, R36.2, STAGE5.1
unnamed: IC4.13 (IN_N), R35.1, R36.1, R38.1
unnamed: IC4.16 (I_BIAS), R37.1
unnamed: C7.2, IC4.10 (B), IC4.12 (OUT)
unnamed: C8.1, IC4.9 (E), R38.2, R39.1, R41.2, STAGE6.1
unnamed: IC5.4 (IN_N), R40.1, R41.1, R43.1
unnamed: IC5.1 (I_BIAS), R42.1
unnamed: C8.2, IC5.5 (OUT), IC5.7 (B)
unnamed: C9.1, IC5.8 (E), R43.2, R44.1, R46.2, STAGE7.1
unnamed: IC5.13 (IN_N), R45.1, R46.1, R48.1
unnamed: IC5.16 (I_BIAS), R47.1
unnamed: C9.2, IC5.10 (B), IC5.12 (OUT)
unnamed: IC5.9 (E), R48.2, R49.1, STAGE8.1, STAGE8_2.1
unnamed: Q2.3 (E), Q3.3 (E), R50.2
unnamed: Q1.2 (B), Q3.1 (C)
unnamed: C10.2, IC1.8 (OUT), R50.1
unnamed: C10.1, IC1.9 (-IN), Q2.1 (C), R51.2
unnamed: CV1.1, R54.1
unnamed: IC1.14 (OUT), Q2.2 (B), R52.2
unnamed: CV2.1, R55.1
unnamed: CV3.1, R56.1
unnamed: IC1.13 (-IN), R52.1, R53.2, R54.2, R55.2, R56.2
unnamed: PRCV_OUT.1, Q1.1 (C)
PE: IC1.3 (+IN), IC1.5 (+IN), IC1.10 (+IN), IC1.12 (+IN), IC2.3 (IN_P), IC2.14 (IN_P), IC3.3 (IN_P), IC3.14 (IN_P), IC4.3 (IN_P), IC4.14 (IN_P), IC5.3 (IN_P), IC5.14 (IN_P), Q1.3 (E), Q3.2 (B), R7.2, R13.2, R20.2, R27.2, R31.2, R35.2, R40.2, R45.2
V+: +V.1, +V2.1, +V3.1, C1.+, C11.2, C13.2, C14.2, C15.2, C16.2, IC1.4 (V+), IC2.11 (V+), IC3.11 (V+), IC4.11 (V+), IC5.11 (V+)
V-: -V.1, -V2.1, -V3.1, C2.-, C12.1, C17.1, C19.1, C22.1, C23.1, IC1.11 (V-), IC2.6 (V-), IC3.6 (V-), IC4.6 (V-), IC5.6 (V-)
